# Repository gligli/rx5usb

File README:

This is the RX5USB project, a Yamaha RX5 DIY programmable waveform cartridge / waveform bank editor.

Everything is under GPL v3 license, except files that have their own license in the header.

The Yamaha RX5 is a mid 80's PCM drum machine ( http://www.vintagesynth.com/yamaha/rx5.php )

This project will allow custom sounds/samples to be played with it.

For more info and binaries, see:
http://electro-music.com/forum/topic-56137.html (English forum) or
http://forum.anafrog.com/phpBB/viewtopic.php?f=36&t=9672 (French forum).

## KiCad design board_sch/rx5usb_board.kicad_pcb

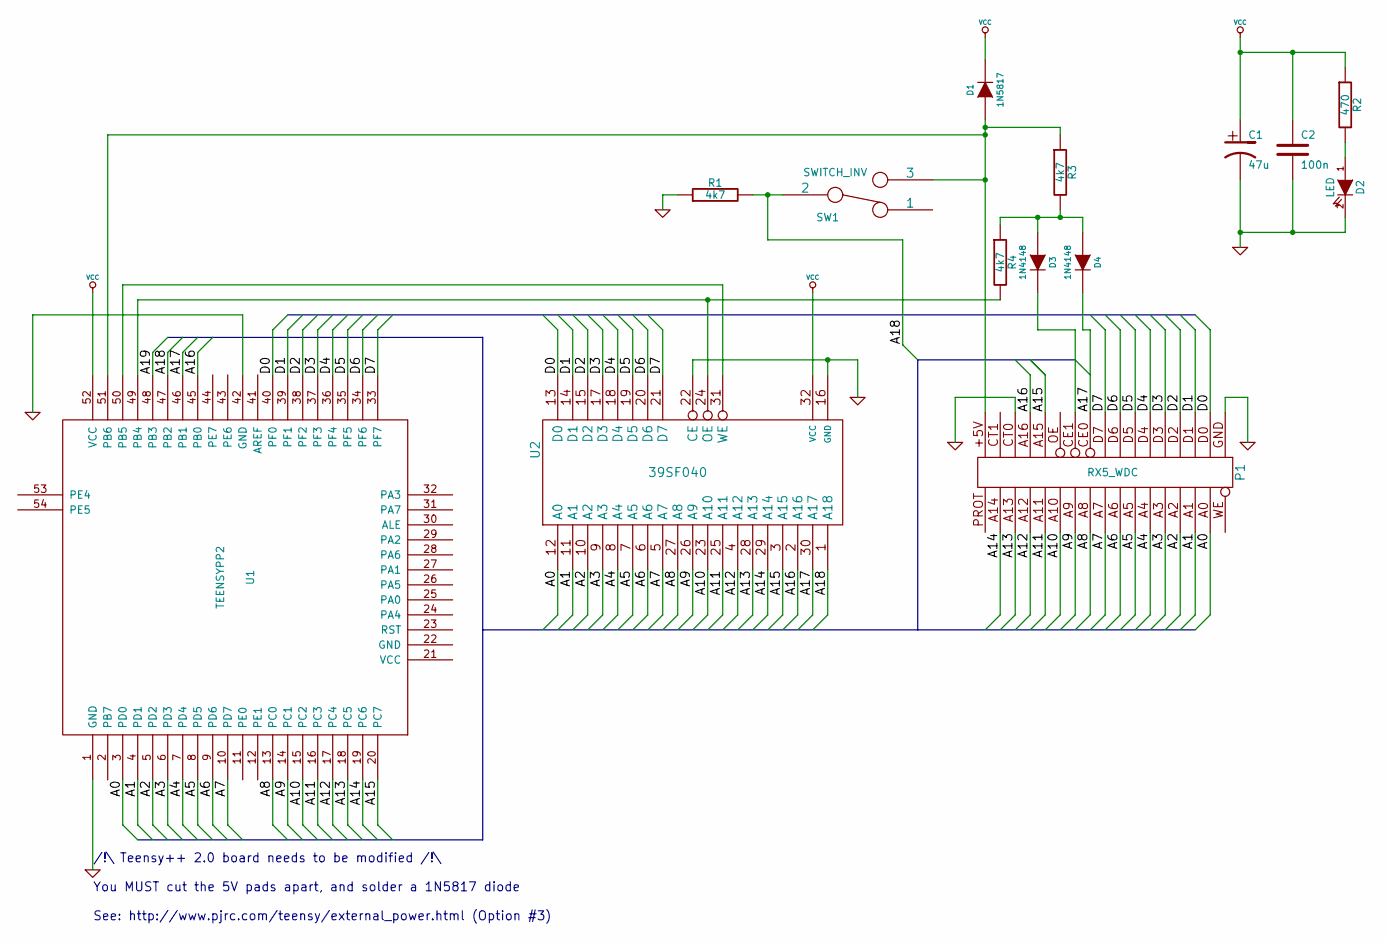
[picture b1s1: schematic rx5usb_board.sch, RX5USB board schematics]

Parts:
C1: 47u
C2: 100n
D1: 1N5817
D2: LED
D3, D4: 1N4148
P1: RX5_WDC
R1, R3, R4: 4k7
R2: 470
SW1: SWITCH_INV
U1: TEENSYPP2; MODULE
U2: 39SF040

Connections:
/A0: P1.A0, U1.3 (PD0), U2.12 (A0)
/A1: P1.A1, U1.4 (PD1), U2.11 (A1)
/A2: P1.A2, U1.5 (PD2), U2.10 (A2)
/A3: P1.A3, U1.6 (PD3), U2.9 (A3)
/A4: P1.A4, U1.7 (PD4), U2.8 (A4)
/A5: P1.A5, U1.8 (PD5), U2.7 (A5)
/A6: P1.A6, U1.9 (PD6), U2.6 (A6)
/A7: P1.A7, U1.10 (PD7), U2.5 (A7)
/A8: P1.A8, U1.13 (PC0), U2.27 (A8)
/A9: P1.A9, U1.14 (PC1), U2.26 (A9)
/A10: P1.A10, U1.15 (PC2), U2.23 (A10)
/A11: P1.A11, U1.16 (PC3), U2.25 (A11)
/A12: P1.A12, U1.17 (PC4), U2.4 (A12)
/A13: P1.A13, U1.18 (PC5), U2.28 (A13)
/A14: P1.A14, U1.19 (PC6), U2.29 (A14)
/A15: P1.A15, U1.20 (PC7), U2.3 (A15)
/A16: P1.A16, U1.45 (PB0), U2.2 (A16)
/A17: D4.2 (K), P1.CE0, U1.46 (PB1), U2.30 (A17)
/A18: R1.2, SW1.2, U1.47 (PB2), U2.1 (A18)
/D0: P1.D0, U1.40 (PF0), U2.13 (D0)
/D1: P1.D1, U1.39 (PF1), U2.14 (D1)
/D2: P1.D2, U1.38 (PF2), U2.15 (D2)
/D3: P1.D3, U1.37 (PF3), U2.17 (D3)
/D4: P1.D4, U1.36 (PF4), U2.18 (D4)
/D5: P1.D5, U1.35 (PF5), U2.19 (D5)
/D6: P1.D6, U1.34 (PF6), U2.20 (D6)
/D7: P1.D7, U1.33 (PF7), U2.21 (D7)
GND: C1.2, C2.2, D2.2 (K), P1.CT0, P1.GND, R1.1, U1.1 (GND), U1.42 (GND), U2.16 (GND), U2.22 (CE)
unnamed: D1.1 (A), P1.+5V, R3.1, SW1.3, U1.51 (PB6)
unnamed: U1.50 (PB5), U2.31 (WE)
unnamed: R4.2, U1.49 (PB4), U2.24 (OE)
unnamed: D3.2 (K), P1.CE1
unnamed: D2.1 (A), R2.2
unnamed: D3.1 (A), D4.1 (A), R3.2, R4.1
VCC: C1.1, C2.1, D1.2 (K), R2.1, U1.52 (VCC), U2.32 (VCC)

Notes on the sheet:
/!\ Teensy++ 2.0 board needs to be modified /!\ You MUST cut the 5V pads apart, and solder a 1N5817 diode See: http://www.pjrc.com/teensy/external_power.html (Option #3)

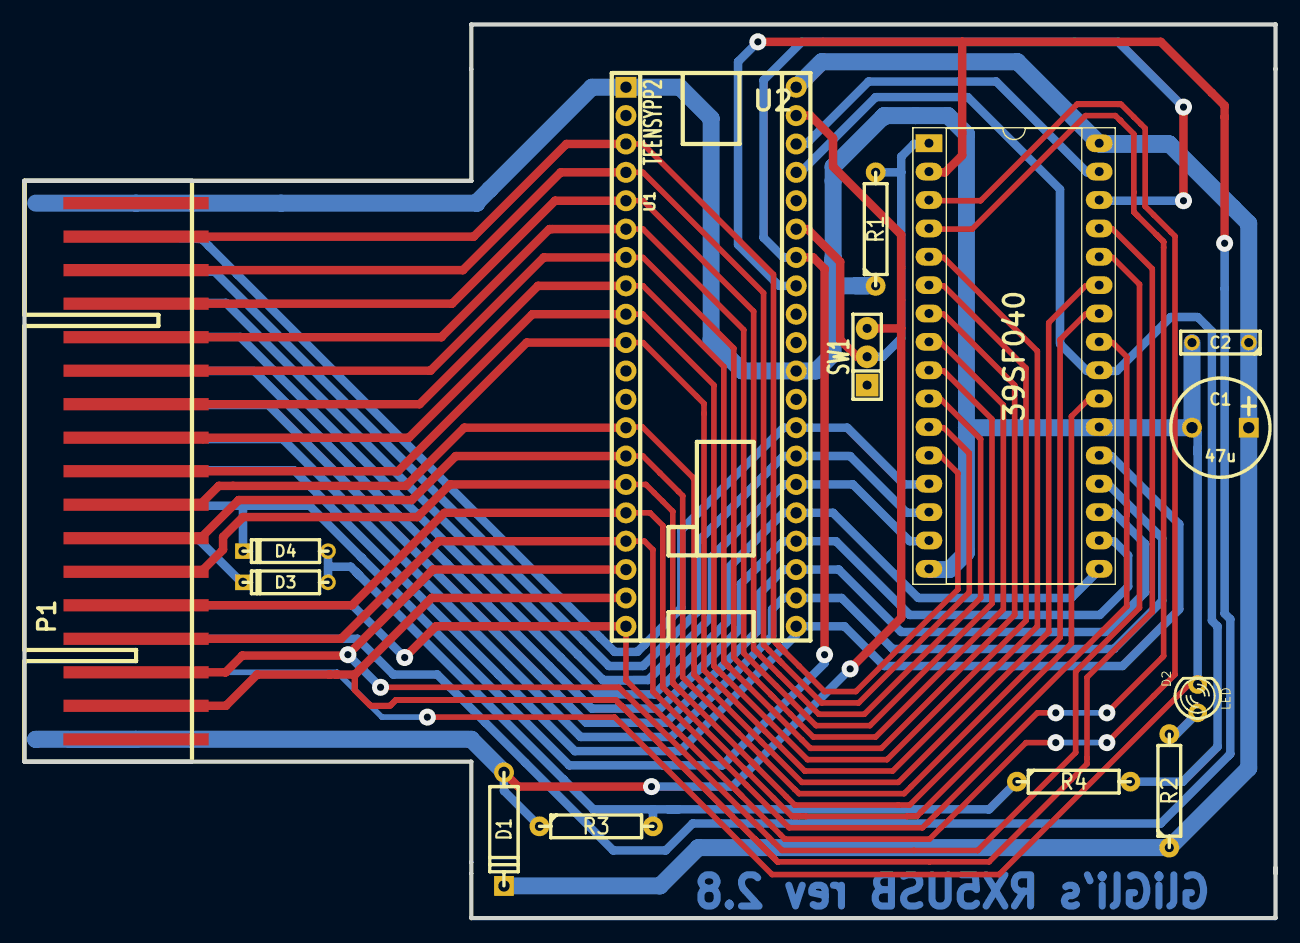
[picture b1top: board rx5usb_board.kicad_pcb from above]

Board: 2 copper layers, 112.0 x 80.0 mm, 14 parts (0 on the bottom side), 35 nets.

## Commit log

2012-12-03 Initial import
2012-12-03 gui_tool: more compatible SDL.dll (down to windows 2000, static runtime)
2012-12-03 adding some various test samples
2012-12-03 gui_tool: autogenerated bank id from header hash / gui fix
2012-12-03 gui_tool: version bump
2012-12-04 adding teensy firmware code
2012-12-04 gui_tool: adding icon
2012-12-04 adding modified PJRC rawhid code (made into a library)
2012-12-04 teensy_fw: program loop
2012-12-04 gui_tool: (untested) bank upload
2012-12-04 Programming seems to work :D
2012-12-04 gui_tool: french version
2012-12-06 Adding board schematics work in progress
2012-12-08 board_sch: PCB refinements (rev 2.7)
2012-12-08 teensy_fw: improvements
2012-12-08 teensy_fw: moving to new flash chip / bugfixes
2012-12-08 banks: adding TR-707 bank
2012-12-08 board_sch: diode-resistor logic sucks... / more uniform res values
2012-12-08 gui_tool: small upload fix / small translation file fix
2012-12-08 Adding project license and short description
2012-12-08 gui_tool: ui refinements / 12bit PCM quality fix
2012-12-08 banks: adding TR-606 bank
2012-12-09 gui_tool: shouldn't be allowed to program an overloaded bank
2012-12-09 gui_tool: banks have a limit on the number of sounds they can contain
2012-12-09 banks: adding LinnDrum banks
2012-12-09 gui_tool: adjust loop start/end when pitch or bps are changed
2012-12-11 adding French install/mount guide
2012-12-13 gui_tool: can now import Fairlight CMI IIx .imd disks / gui fixes
2012-12-14 gui_tool: CMI import fix
2012-12-14 gui_tool: regular sample import fix
2012-12-15 teensy_fw: more reliable way to detect RX5 power
2012-12-16 gui_tool: using SRC, a much better audio resampler than SDL / moving back to vanilla SDL 1.2.15 / misc changes
2012-12-22 gui_tool: using custom 0.1.8 libsamplerate.dll , fixes crashes
2012-12-22 gui_tool: preparing beta 1 release
2012-12-22 board_sch: minor change
2012-12-22 documentation: french guide changes
2012-12-22 adding English install/mount guide
2012-12-22 adding readmes
2012-12-22 gui_tool: fixed the new SRC dll crashing on Windows 2000/XP
2016-10-17 firmware USB detection fix -- programming speedup
2016-10-17 tool: custom programming -- other fixes
2016-10-30 gui tool project update
2021-08-24 Converted files to modern KiCad format
2021-08-24 Fix solder mask issue
2021-08-24 Fixed footprint associations
2021-08-24 Rename footprints
